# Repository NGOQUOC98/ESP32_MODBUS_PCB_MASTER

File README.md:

# ESP32_MODBUS_PCB_MASTER
# PAS sprinkler / irrigation controller

## Pin Wiring  

| PIN NAME | RS485_U2TX | RS485_U2RX | RS485_U2EN | RS485_U1TX | RS485_U1RX | RS485_U1EN | OPAMP_VA1 | OPAMP_IA0 |
| -------- | ---------- | ---------- | ---------- | ---------- | ---------- | ---------- | --------- | --------- |
| PIN NUM  | GPIO22     | GPIO23     | GPIO19     | GPIO18     | GPIO10     | GPIO5      | GPIO34    | GPIO35    |

<br/>

| PIN NAME | RELAY_OUT0 | RELAY_OUT1 | RELAY_OUT2 | RELAY_OUT3 | RELAY_OUT4 | RELAY_OUT5 | RELAY_OUT6 | RELAY_OUT7 |
| -------- | ---------- | ---------- | ---------- | ---------- | ---------- | ---------- | ---------- | ---------- |
| PIN NUM  | GPIO33     | GPIO25     | GPIO32     | GPIO13     | GPIO15     | GPIO26     | GPIO4      | GPIO9      |

<br/>

| PIN NAME | GPIO_EX0 | GPIO_EX1 | GPIO_EX2 | GPIO_EX3 | DS1307_SCL | DS1307_SDA |
| -------- | -------- | -------- | -------- | -------- | ---------- | ---------- |
| PIN NUM  | GPIO39   | GPIO38   | GPIO37   | GPIO36   | GPIO27     | GPIO14     |

## Hardware

### Schematics

### PCB Layout
#### Top side

#### Back side

### 3D

#### Top side

#### Back side

### Gerber

Version 3.0

- [Gerber V3
.0](./assets/gerber/PAS_v3.0.rar)

### Remark

This project was in development phase - we will remove this remark after release

# License

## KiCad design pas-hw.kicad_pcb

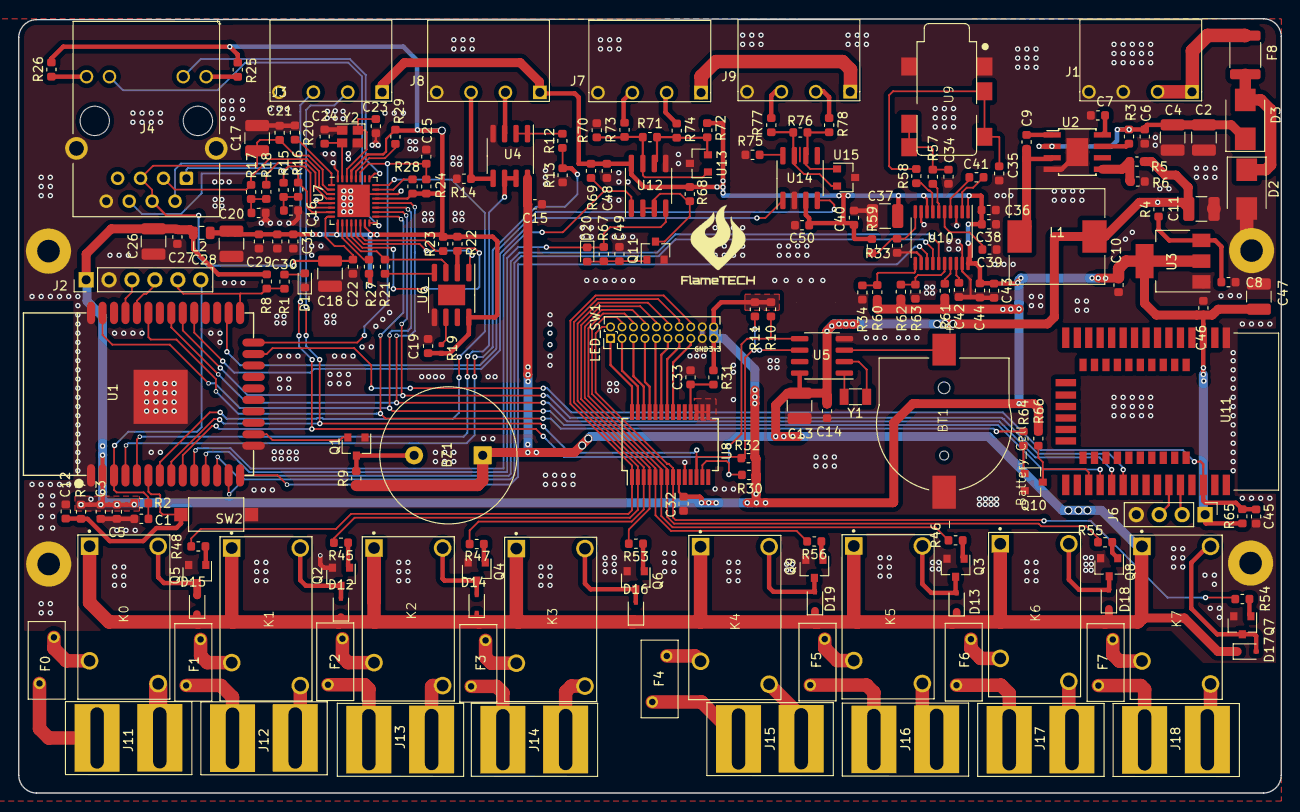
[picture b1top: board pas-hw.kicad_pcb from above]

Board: 2 copper layers, 139.9 x 85.8 mm, 198 parts (0 on the bottom side), 153 nets.

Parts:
BT1: Battery_Cell; BAT_CR1220_Holder
BZ1: Buzzer; Buzzer_15x7.5RM7.6
C1, C3, C5, C12: C_Small; C_0603_1608Metric
C2, C4: 10uF/50V; C_1210_3225Metric
C6, C7, C8, C9, C10, C14, C15, C16, C19, C20, C21, C22, C25, C27, C29, C30, C31, C32, C33, C38, C40, C42, C44, C45, C46, C48, C50: 100nF; C_0603_1608Metric
C11, C17, C18, C26, C28: 47uF; C_1210_3225Metric
C13, C37, C47: 10uF; C_1210_3225Metric
C23, C24: 20pF; C_0603_1608Metric
C34, C35, C36, C39, C41, C43: 2.2uF; C_0603_1608Metric
C49: 1nF; C_0603_1608Metric
D1: LED_STT1; LED_0603_1608Metric
D2: TVS 18V; D_SMB
D3: SS34; D_SMB
D12, D13, D14, D15, D16, D17, D18, D19: 1N4148; D_SOD-323
D20: DIODE; D_0603_1608Metric
F0, F1, F2, F3, F4, F5, F6, F7: Fuse_Small; Fuse_BelFuse_0ZRE0005FF_L8.3mm_W3.8mm
F8: Fuse_Small; Fuse_1812_4532Metric
H5, H6, H7, H8: MountingHole_Pad; MountingHole_2.5mm_Pad
J1: POWER; connect_1x4_3.81mm
J2: FLASH_HEADER; PinHeader_1x06_P2.54mm_Vertical
J3: I2C; connect_1x4_3.81mm
J4: RJ45_LED_Shielded; RJ45_Hanrun_HR911105A
J6: Conn_01x04; PinHeader_1x04_P2.54mm_Vertical
J7: RS485; connect_1x4_3.81mm
J8: Analog; connect_1x4_3.81mm
J9: CAN; connect_1x4_3.81mm
J11: Relay_0; pin_1x1_6mm
J12: Relay_1; pin_1x1_6mm
J13: Relay_2; pin_1x1_6mm
J14: Relay_3; pin_1x1_6mm
J15: Relay_4; pin_1x1_6mm
J16: Relay_5; pin_1x1_6mm
J17: Relay_6; pin_1x1_6mm
J18: Relay_7; pin_1x1_6mm
K0, K1, K2, K3, K4, K5, K6, K7: 10A; relay-10A-18.2x10x14
L1: 15uH/3A; L_10.4x10.4_H4.8
L2: 600uH/200mA; L_0805_2012Metric
LED_SW1: Conn_02x10_Counter_Clockwise; connect_2x10_P1.27mm_Vertical
Logo1: Logo_flametech; logo-flametech-v1
Q1: 2N2219; SOT-23
Q2, Q3, Q4, Q5, Q6, Q7, Q8, Q9, Q10, Q11: BSS138; SOT-23
R1, R25, R26, R57, R58: 470R; R_0603_1608Metric
R2, R7, R9, R75: R_Small; R_0603_1608Metric
R3: 100K; R_0603_1608Metric
R4, R63: 0R; R_0603_1608Metric
R5: 44K2; R_0603_1608Metric
R6, R8, R21, R31, R59, R60, R61, R62, R65, R67, R68, R69: 10K; R_0603_1608Metric
R10, R11, R24, R27, R28, R29, R30, R32: 4K7; R_0603_1608Metric
R12, R13, R14: TBD; R_0603_1608Metric
R15, R16, R17, R18: 49.9R/1%; R_0603_1608Metric
R19: 4K7; R_0402_1005Metric
R20: 6K8/1%; R_0603_1608Metric
R22, R23: 4K7/NC; R_0603_1608Metric
R33, R34: NC; R_0603_1608Metric
R45, R46, R47, R48, R53, R54, R55, R56, R64: 10; R_0603_1608Metric
R66, R70, R72: 1K; R_0603_1608Metric
R71, R76: 120R; R_0603_1608Metric
R73, R74, R77, R78: PTC; R_0603_1608Metric
SW2: SW_Push; SW_SPST_CK_RS282G05A3
U1: ESP32-WROVER; ESP32-WROOM
U2: FR9888; TI_SO-PowerPAD-8
U3: AMS1117-3.3; SOT-223-3_TabPin2
U4: LM358; SOIC-8_3.9x4.9mm_P1.27mm
U5: DS1307Z+; SOIC-8_3.9x4.9mm_P1.27mm
U6: 93LC46; SOIC-8-1EP_3.9x4.9mm_P1.27mm_EP2.29x3mm
U7: DM9051; QFN-32-1EP_5x5mm_P0.5mm_EP3.6x3.6mm
U8: MCP23017_SS; SSOP-28_5.3x10.2mm_P0.65mm
U9: AudioJack; jack3.5
U10: PCM510x; TSSOP-20_4.4x6.5mm_P0.65mm
U11: NRF52833; Module_NRF52833_SMD
U12: MAX3485; SOIC-8_3.9x4.9mm_P1.27mm
U13: SM712; SOT-23
U14: SN65HVD230; SOIC-8_3.9x4.9mm_P1.27mm
U15: NUP2105L; SOT-23
Y1: Crystal; Crystal_SMD_3215-2Pin_3.2x1.5mm
Y2: 25 MHz; Crystal_SMD_2520-4Pin_2.5x2.0mm

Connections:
+1V8: C17.1, C18.1, C21.1, C22.1, J4.4, J4.5, U7.2, U7.8
+3V3: C3.1, C5.1, C10.1, C26.1, C27.1, C32.1, C36.1, C37.1, C38.1, C40.1, C43.1, C44.1, C46.1, C47.1, C48.1, C50.1, J2.1, J3.1, J6.1, J8.1, L2.1, LED_SW1.10, LED_SW1.11, R2.1, R7.1, R8.1, R10.1, R11.1, R30.1, R31.1, R32.1, R59.1, R60.1, R61.1, R62.1, R65.1, R66.1, R68.1, R69.1, R72.2, U1.2, U3.2, U8.9, U10.1, U10.8, U10.20, U11.34, U12.8, U14.3
+5V: BZ1.1, C11.1, C13.1, C14.1, C15.1, D12.1, D13.1, D14.1, D15.1, D16.1, D17.1, D18.1, D19.1, K0.1, K1.1, K2.1, K3.1, K4.1, K5.1, K6.1, K7.1, L1.2, R4.2, R5.1, R9.1, U4.8, U5.8
+12V: J7.1, J9.1
ANALOG_1: J8.2, U4.3
ANALOG_2: J8.3, R14.2, U4.5
BUTTON: C12.1, R7.2, SW2.2, U1.6
BUZZER: Q1.2, U1.16
CAN_H: J9.3, R77.2
CAN_L: J9.2, R78.2
CAN_RX: U1.26, U14.4
CAN_TX: U1.29, U14.1
ETH_SPI_INT: U1.7, U7.24
ETH_SPI_RST: C25.1, R24.2, U1.24, U7.27
FLASH_EN: C1.1, J2.6, R2.2, U1.3
FLASH_IO0: J2.5, R1.2, R8.2, U1.25
FLASH_U0RX: J2.4, U1.34
FLASH_U0TX: J2.3, U1.35
GND: BT1.2, C1.2, C2.2, C3.2, C4.2, C5.2, C6.2, C7.2, C8.2, C10.2, C11.2, C12.2, C13.2, C14.2, C15.2, C16.2, C17.2, C18.2, C19.1, C20.2, C21.2, C22.2, C23.2, C24.2, C25.2, C26.2, C27.2, C28.2, C29.2, C30.2, C31.2, C32.2, C33.2, C34.2, C35.2, C36.2, C37.2, C38.2, C39.1, C40.2, C42.1, C43.2, C44.2, C45.2, C46.2, C47.2, C48.2, C49.2, C50.2, D1.1, D2.2, H5.1, H6.1, H7.1, H8.1, J1.3, J1.4, J2.2, J3.4, J4.8, J4.SH, J6.4, J7.4, J8.4, J9.4, LED_SW1.9, LED_SW1.12, Q1.1, Q2.2, Q3.2, Q4.2, Q5.2, Q6.2, Q7.2, Q8.2, Q9.2, Q10.2, Q11.2, R6.2, R13.1, R14.1, R20.2, R33.2, R34.1, R63.2, R70.1, R75.2, SW2.1, U1.1, U1.15, U1.38, U1.39, U2.4, U2.9, U3.1, U4.4, U5.4, U6.5, U7.5, U7.22, U7.32, U7.33, U8.10, U8.15, U8.16, U8.17, U9.1, U9.4, U10.3, U10.9, U10.12, U10.19, U11.36, U12.5, U13.3, U14.2, U15.3, Y2.2, Y2.4
GP1: R27.1, U7.10
GP2: R28.1, U7.23
GP3: R29.1, U7.28
I2C_SCL: J3.2, R11.2, R32.2, U1.8, U5.6, U8.12
I2C_SDA: J3.3, R10.2, R30.2, U1.9, U5.5, U8.13
I2S_BCK: U1.14, U10.13
I2S_DATA: U1.13, U10.14
I2S_LRCK: U1.12, U10.15
LED1+: J4.9, R25.1
LED1_LINK: J4.10, U7.25
LED2+: J4.12, R26.1
LED2_FDX: J4.11, U7.16
unnamed: BT1.1, U5.3
unnamed: BZ1.2, Q1.3, R9.2
unnamed: C2.1, C4.1, C6.1, D3.1, R3.2, U2.2
unnamed: C7.1, U2.8
unnamed: C8.1, R4.1, U3.3
unnamed: C9.1, U2.1
unnamed: C9.2, L1.1, U2.3
unnamed: C16.1, R15.2, R16.2
unnamed: C20.1, R17.2, R18.2
unnamed: C23.1, U7.30, Y2.1
unnamed: C24.1, U7.31, Y2.3
unnamed: C33.1, R31.2, U8.18
unnamed: C34.1, R57.2, U9.2, U9.5
unnamed: C35.1, R58.2, U9.3, U9.6
unnamed: C39.2, U10.5
unnamed: C41.1, U10.2
unnamed: C41.2, U10.4
unnamed: C42.2, U10.18
unnamed: C49.1, D20.2, Q11.1, R67.1
unnamed: D1.2, R1.1
unnamed: D2.1, D3.2, F8.2
unnamed: D12.2, K1.2, Q2.3
unnamed: D13.2, K5.2, Q3.3
unnamed: D14.2, K2.2, Q4.3
unnamed: D15.2, K0.2, Q5.3
unnamed: D16.2, K3.2, Q6.3
unnamed: D17.2, K7.2, Q7.3
unnamed: D18.2, K6.2, Q8.3
unnamed: D19.2, K4.2, Q9.3
unnamed: F0.1, K0.3
unnamed: F1.1, K1.3
unnamed: F2.1, K2.3
unnamed: F3.2, K3.3
unnamed: F4.2, K4.3
unnamed: F5.1, K5.3
unnamed: F6.2, K6.3
unnamed: F7.2, K7.3
unnamed: F8.1, J1.1, J1.2
unnamed: J4.1, R15.1, U7.6
unnamed: J4.2, R16.1, U7.7
unnamed: J4.3, R17.1, U7.3
unnamed: J4.6, R18.1, U7.4
unnamed: Q2.1, R45.1
unnamed: Q3.1, R46.1
unnamed: Q4.1, R47.1
unnamed: Q5.1, R48.1
unnamed: Q6.1, R53.1
unnamed: Q7.1, R54.1
unnamed: Q8.1, R55.1
unnamed: Q9.1, R56.1
unnamed: Q10.1, R64.2
unnamed: Q10.3, R66.2, U11.13
unnamed: Q11.3, R68.2, U12.2, U12.3
unnamed: R3.1, U2.7
unnamed: R5.2, R6.1, U2.5
unnamed: R12.2, U4.1, U4.2
unnamed: R19.1, U6.6
unnamed: R20.1, U7.1
unnamed: R21.1, U6.3, U7.11
unnamed: R21.2, U6.4
unnamed: R22.1, U6.2, U7.12
unnamed: R23.1, U7.14
unnamed: R33.1, R59.2, U10.10
unnamed: R34.2, R60.2, U10.11
unnamed: R57.1, U10.6
unnamed: R58.1, U10.7
unnamed: R61.2, U10.17
unnamed: R62.2, R63.1, U10.16
unnamed: R70.2, R71.1, R73.1, U12.7, U13.1
unnamed: R71.2, R72.1, R74.1, U12.6, U13.2
unnamed: R75.1, U14.8
unnamed: R76.1, R77.1, U14.7, U15.2
unnamed: R76.2, R78.1, U14.6, U15.1
unnamed: U5.1, Y1.1
unnamed: U5.2, Y1.2
unnamed: U6.1, U7.13
OPAMP_IA0: U1.5, U4.6, U4.7
OPAMP_VA1: R12.1, R13.2, U1.4
P0: F0.2, J11.1
P1: J11.2, K0.4
P2: F1.2, J12.1
P3: J12.2, K1.4
P4: F2.2, J13.1
P5: J13.2, K2.4
P6: F3.1, J14.1
P7: J14.2, K3.4
P8: F4.1, J15.1
P9: J15.2, K4.4
P10: F5.2, J16.1
P11: J16.2, K5.4
P12: F6.1, J17.1
P13: J17.2, K6.4
P14: F7.1, J18.1
P15: J18.2, K7.4
RELAY_OUT0: LED_SW1.20, R54.2, U8.8
RELAY_OUT1: LED_SW1.19, R55.2, U8.7
RELAY_OUT2: LED_SW1.18, R46.2, U8.6
RELAY_OUT3: LED_SW1.17, R56.2, U8.5
RELAY_OUT4: LED_SW1.16, R53.2, U8.4
RELAY_OUT5: LED_SW1.15, R47.2, U8.3
RELAY_OUT6: LED_SW1.14, R45.2, U8.2
RELAY_OUT7: LED_SW1.13, R48.2, U8.1
RS485_A: J7.2, R74.2
RS485_B: J7.3, R73.2
RS485_RX: R69.2, U1.10, U12.1
RS485_TX: D20.1, R67.2, U1.11, U12.4
SPI_CLK: U1.30, U7.18, U11.10
SPI_CS: R64.1, U1.33, U7.17
SPI_MISO: U1.31, U7.20, U11.11
SPI_MOSI: U1.37, U7.19, U11.12
SW0: LED_SW1.1, U8.28
SW1: LED_SW1.2, U8.27
SW2: LED_SW1.3, U8.26
SW3: LED_SW1.4, U8.25
SW4: LED_SW1.5, U8.24
SW5: LED_SW1.6, U8.23
SW6: LED_SW1.7, U8.22
SW7: LED_SW1.8, U8.21
SWCLK: J6.2, U11.5
SWDIO: J6.3, U11.6
VCC: C19.2, C28.1, C29.1, C30.1, C31.1, L2.2, R19.2, R22.2, R23.2, R24.1, R25.2, R26.2, R27.2, R28.2, R29.2, U6.8, U7.9, U7.15, U7.21, U7.29
ZIGBEE_RST: C45.1, R65.2, U1.23, U11.3

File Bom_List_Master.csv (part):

Source:,C:\Users\NGO CUONG\Desktop\Master\pas-hw\pas-hw.sch,,,,,
Date:,9/16/2020 14:31,,,,,
Tool:,Eeschema (5.1.6)-1,,,,,
Generator:,C:\Program Files\KiCad\bin\scripting\plugins/bom_csv_grouped_by_value_with_fp.py,,,,,
Component Count:,198,,,,,
Ref,Qnty,Value,Cmp name,Footprint,Description,Vendor
"BT1, ",1,CR1220,Battery_Cell,footrint_master:BAT_CR1220_Holder,Single-cell battery,
"BZ1, ",1,Buzzer,Buzzer,Buzzer_Beeper:Buzzer_15x7.5RM7.6,"Buzzer, polarized",
"C1, C3, C6, C7, C8, C9, C10, C12, C14, C15, C16, C19, C20, C21, C22, C25, C27, C29, C30, C31, C32, C33, C38, C40, C42, C44, C45, C46, C48, C50, ",30,100nF,C_Small,Capacitor_SMD:C_0603_1608Metric,"Unpolarized capacitor, small symbol",
"C2, C4, ",2,10uF/50V,CP_Small,Capacitor_SMD:C_1210_3225Metric,"Polarized capacitor, small symbol",
"C5, ",1,10uF,C_Small,Capacitor_SMD:C_0603_1608Metric,"Unpolarized capacitor, small symbol",
"C11, C17, C18, C26, C28, ",5,47uF,C_Small,Capacitor_SMD:C_1210_3225Metric,"Unpolarized capacitor, small symbol",
"C13, C37, C47, ",3,10uF,C_Small,Capacitor_SMD:C_1210_3225Metric,"Unpolarized capacitor, small symbol",
"C23, C24, ",2,20pF,C_Small,Capacitor_SMD:C_0603_1608Metric,"Unpolarized capacitor, small symbol",
"C34, C35, C36, C39, C41, C43, ",6,2.2uF,C_Small,Capacitor_SMD:C_0603_1608Metric,"Unpolarized capacitor, small symbol",
"C49, ",1,1nF,C_Small,Capacitor_SMD:C_0603_1608Metric,"Unpolarized capacitor, small symbol",
"D1, ",1,LED_STT1,LED_Small,LED_SMD:LED_0603_1608Metric,"Light emitting diode, small symbol",
"D2, ",1,TVS 18V,D_Schottky_Small,Diode_SMD:D_SMB,"Schottky diode, small symbol",
"D3, ",1,SS34,D_Small,Diode_SMD:D_SMB,"Diode, small symbol",
"D12, D13, D14, D15, D16, D17, D18, D19, ",8,1N4148,1N4148,Diode_SMD:D_SOD-323,"100V 0.15A standard switching diode, DO-35",
"D20, ",1,TVS 18V,D_Schottky_Small,Diode_SMD:D_0603_1608Metric,"Schottky diode, small symbol",
"F0, F1, F2, F3, F4, F5, F6, F7, ",8,10A 250VAC,Fuse_Small,Fuse:Fuse_BelFuse_0ZRE0005FF_L8.3mm_W3.8mm,"Fuse, small symbol",
"F8, ",1,24V/3A,Fuse_Small,Fuse:Fuse_1812_4532Metric,"Fuse, small symbol",
"H5, H6, H7, H8, ",4,MountingHole_Pad,MountingHole_Pad,MountingHole:MountingHole_2.5mm_Pad,Mounting Hole with connection,
"J1, ",1,POWER,Conn_01x04,footrint_master:connect_1x4_3.81mm,"Generic connector, single row, 01x04, script generated (kicad-library-utils/schlib/autogen/connector/)",
"J2, ",1,FLASH_HEADER,Conn_01x06,Connector_PinHeader_2.54mm:PinHeader_1x06_P2.54mm_Vertical,"Generic connector, single row, 01x06, script generated (kicad-library-utils/schlib/autogen/connector/)",
"J3, ",1,I2C,Conn_01x04,footrint_master:connect_1x4_3.81mm,"Generic connector, single row, 01x04, script generated (kicad-library-utils/schlib/autogen/connector/)",
"J4, ",1,RJ45_LED_Shielded,RJ45_LED_Shielded,Connector_RJ:RJ45_Hanrun_HR911105A,"RJ connector, 8P8C (8 positions 8 connected), two LEDs, Shielded",
"J6, ",1,Conn_01x04,Conn_01x04,Connector_PinHeader_2.54mm:PinHeader_1x04_P2.54mm_Vertical,"Generic connector, single row, 01x04, script generated (kicad-library-utils/schlib/autogen/connector/)",
"J7, ",1,RS485,Conn_01x04,footrint_master:connect_1x4_3.81mm,"Generic connector, single row, 01x04, script generated (kicad-library-utils/schlib/autogen/connector/)",
"J8, ",1,Analog,Conn_01x04,footrint_master:connect_1x4_3.81mm,"Generic connector, single row, 01x04, script generated (kicad-library-utils/schlib/autogen/connector/)",
"J9, ",1,CAN,Conn_01x04,footrint_master:connect_1x4_3.81mm,"Generic connector, single row, 01x04, script generated (kicad-library-utils/schlib/autogen/connector/)",
"J11, ",1,Relay_0,Conn_01x02,footrint_master:pin_1x1_6mm,"Generic connector, single row, 01x02, script generated (kicad-library-utils/schlib/autogen/connector/)",
"J12, ",1,Relay_1,Conn_01x02,footrint_master:pin_1x1_6mm,"Generic connector, single row, 01x02, script generated (kicad-library-utils/schlib/autogen/connector/)",
"J13, ",1,Relay_2,Conn_01x02,footrint_master:pin_1x1_6mm,"Generic connector, single row, 01x02, script generated (kicad-library-utils/schlib/autogen/connector/)",
"J14, ",1,Relay_3,Conn_01x02,footrint_master:pin_1x1_6mm,"Generic connector, single row, 01x02, script generated (kicad-library-utils/schlib/autogen/connector/)",
"J15, ",1,Relay_4,Conn_01x02,footrint_master:pin_1x1_6mm,"Generic connector, single row, 01x02, script generated (kicad-library-utils/schlib/autogen/connector/)",
"J16, ",1,Relay_5,Conn_01x02,footrint_master:pin_1x1_6mm,"Generic connector, single row, 01x02, script generated (kicad-library-utils/schlib/autogen/connector/)",
"J17, ",1,Relay_6,Conn_01x02,footrint_master:pin_1x1_6mm,"Generic connector, single row, 01x02, script generated (kicad-library-utils/schlib/autogen/connector/)",
"J18, ",1,Relay_7,Conn_01x02,footrint_master:pin_1x1_6mm,"Generic connector, single row, 01x02, script generated (kicad-library-utils/schlib/autogen/connector/)",
"K0, K1, K2, K3, K4, K5, K6, K7, ",8,10A,RELAY_MIN1-Relays,footrint_master:relay-10A-18.2x10x14,,
"L1, ",1,15uH/3A,L_Small,Inductor_SMD:L_10.4x10.4_H4.8,"Inductor, small symbol",
"L2, ",1,600uH/200mA,L_Small,Inductor_SMD:L_0805_2012Metric,"Inductor, small symbol",
"LED_SW1, ",1,Conn_02x10_Counter_Clockwise,Conn_02x10_Counter_Clockwise,footrint_master:connect_2x10_P1.27mm_Vertical,"Generic connector, double row, 02x10, counter clockwise pin numbering scheme (similar to DIP packge numbering), script generated (kicad-library-utils/schlib/autogen/connector/)",
"Logo1, ",1,Logo_flametech,Logo_IoTMaker-logo_iotmaker,footrint_master:logo-flametech-v1,,
"Q1, ",1,2N2219,2N2219,Package_TO_SOT_SMD:SOT-23,"800mA Ic, 50V Vce, NPN Transistor, TO-39",
"Q2, Q3, Q4, Q5, Q6, Q7, Q8, Q9, Q10, Q11, ",10,BSS138,BSS138,Package_TO_SOT_SMD:SOT-23,"50V Vds, 0.22A Id, N-Channel MOSFET, SOT-23",
"R1, R25, R26, R57, R58, ",5,470R,R_Small,Resistor_SMD:R_0603_1608Metric,"Resistor, small symbol",
"R2, R5, R9, ",3,10k,R_Small,Resistor_SMD:R_0603_1608Metric,"Resistor, small symbol",
"R3, ",1,100K,R_Small,Resistor_SMD:R_0603_1608Metric,"Resistor, small symbol",
"R4, R63, ",2,0R,R_Small,Resistor_SMD:R_0603_1608Metric,"Resistor, small symbol",
"R6, R7, R8, R21, R31, R59, R60, R61, R62, R65, R67, R68, R69, ",13,10K,R_Small,Resistor_SMD:R_0603_1608Metric,"Resistor, small symbol",
"R10, R11, R24, R27, R28, R29, R30, R32, ",8,4K7,R_Small,Resistor_SMD:R_0603_1608Metric,"Resistor, small symbol",
"R12, R13, R14, ",3,120R/100mW,R_Small,Resistor_SMD:R_0603_1608Metric,"Resistor, small symbol",
"R15, R16, R17, R18, ",4,49.9R/1%,R_Small,Resistor_SMD:R_0603_1608Metric,"Resistor, small symbol",
"R19, ",1,4K7,R_Small,Resistor_SMD:R_0402_1005Metric,"Resistor, small symbol",
"R20, ",1,6K8/1%,R_Small,Resistor_SMD:R_0603_1608Metric,"Resistor, small symbol",
"R22, R23, ",2,4K7/NC,R_Small,Resistor_SMD:R_0603_1608Metric,"Resistor, small symbol",
"R33, R34, ",2,NC,R_Small,Resistor_SMD:R_0603_1608Metric,"Resistor, small symbol",
"R45, R46, R47, R48, R53, R54, R55, R56, R64, ",9,10R,R_Small,Resistor_SMD:R_0603_1608Metric,"Resistor, small symbol",
"R66, R70, R72, ",3,1K,R_Small,Resistor_SMD:R_0603_1608Metric,"Resistor, small symbol",
"R71, R76, ",2,120R,R_Small,Resistor_SMD:R_0603_1608Metric,"Resistor, small symbol",
"R73, R74, R77, R78, ",4,PTC,R_Small,Resistor_SMD:R_0603_1608Metric,"Resistor, small symbol",
"R75, ",1,100nF,R_Small,Resistor_SMD:R_0603_1608Metric,"Resistor, small symbol",
"SW2, ",1,SW_Push,SW_Push,Button_Switch_SMD:SW_SPST_CK_RS282G05A3,"Push button switch, generic, two pins",
"U1, ",1,ESP32-WROVER,ESP32-WROVER-esp32-wrover,footrint_master:ESP32-WROOM,,
"U2, ",1,FR9888,TPS54336ADDA,Package_SO:TI_SO-PowerPAD-8," 4.5V to 28V Input, 3A, Synchronous Step-Down Converter with Eco-mode(tm)",
"U3, ",1,AMS1117-3.3,AMS1117-3.3,Package_TO_SOT_SMD:SOT-223-3_TabPin2,"1A Low Dropout regulator, positive, 3.3V fixed output, SOT-223",
"U4, ",1,LM358,LM358,Package_SO:SOIC-8_3.9x4.9mm_P1.27mm,"Low-Power, Dual Operational Amplifiers, DIP-8/SOIC-8/TO-99-8",
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
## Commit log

2020-10-14 add file
2020-10-14 edit readme
2021-01-09 edit file
